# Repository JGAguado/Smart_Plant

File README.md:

# Smart Plant

**See how your plant is doing — on its own e-paper label and in Home Assistant.**

Smart Plant measures soil moisture, light, temperature and humidity. Place it
in your plant pot, read the measurements on the 2.9-inch e-paper display,
and connect it to Home Assistant with ESPHome.

**[Get started](https://smart-plant.readthedocs.io/en/v2r1/getting_started.html)**
· **[Create your plant label](https://github.com/JGAguado/Label-maker)**
· **[Get a board](https://www.elecrow.com/smart-plant.html)**
· **[Read the documentation](https://smart-plant.readthedocs.io/en/v2r1/)**

## A useful label for every plant

- **Check the soil and surroundings.** Read soil moisture, ambient light,
  air temperature and relative humidity.
- **Read it at the pot.** The e-paper screen shows the last displayed readings
  while the device sleeps.
- **Make it yours.** Give each plant its own name, illustration and gauge
  background with the companion Label-maker project.
- **Connect to Home Assistant.** Choose the native ESPHome API or retained
  MQTT readings for devices that spend most of their time asleep.
- **Run on battery.** The firmware sleeps between measurement cycles.
  The hardware also supports an optional solar cell.

## Start with one plant

1. [Get a board](https://www.elecrow.com/smart-plant.html), or use the
   [hardware design files](Design/) to explore the board.
2. Follow the [getting-started guide](https://smart-plant.readthedocs.io/en/v2r1/getting_started.html)
   and [ESPHome programming guide](https://smart-plant.readthedocs.io/en/v2r1/programming.html).
3. Set your Wi-Fi credentials and calibrate the soil sensor for your setup.
4. Add your own label background, then install the firmware.

The [standalone configuration](docs/source/files/configuration.yaml) is the
starting point for a single device. Read the
[safety instructions](https://smart-plant.readthedocs.io/en/v2r1/safety.html)
before assembly and flashing.

## Create your plant label

The companion **[Label-maker](https://github.com/JGAguado/Label-maker)**
generates printable plant labels and e-paper backgrounds from JSON or YAML
templates. Use it to add a plant name and illustration to your display.

Follow the [step-by-step label guide](docs/source/labels.rst).
Start with the [plant examples and generator](https://github.com/JGAguado/Label-maker/tree/main/1_Plants),
then follow the programming guide to use the resulting background image.
The firmware draws the live readings over that image.

## Connect one plant or several

| Setup | Starting point | During deep sleep |
| --- | --- | --- |
| One device with the native ESPHome API | [Standalone configuration](docs/source/files/configuration.yaml) | No network response; entity availability depends on Home Assistant setup. |
| Several devices with retained MQTT readings | [MQTT example](examples/multi-device/my-lemon-tree.yaml) | Last published readings remain available. |
| Shared packages with the native ESPHome API | [API example](examples/multi-device/my-lemon-tree-api.yaml) | No network response; entity availability depends on Home Assistant setup. |

The [multi-device guide](examples/multi-device/README.md) explains the shared
hardware core and transport profiles. Each device sets its identity and
credentials. Calibration and label images use shared defaults unless overridden.

## Explore the hardware

Smart Plant combines an ESP32-S2, a soil-moisture probe, environmental sensors
and an e-paper display. The repository includes board design files and
printable enclosure models.

- [Board design](Design/)
- [Enclosure models](Enclosure/)
- [Schematics and supporting files](Documentation/)
- [Technical specifications](https://smart-plant.readthedocs.io/en/v2r1/specs.html)
- [Assembly guide](https://smart-plant.readthedocs.io/en/v2r1/assembly.html)

## Questions and contributions

Use [Discussions](https://github.com/JGAguado/Smart_Plant/discussions) for
questions and ideas. Report reproducible problems in
[Issues](https://github.com/JGAguado/Smart_Plant/issues).

Contributions to firmware, documentation and examples are welcome. Describe
the problem, the change and how you verified it in your pull request.

Created by [J. G. Aguado](https://github.com/JGAguado), with contributions
from the community.

## License

This project uses [CC BY-NC-SA 4.0](LICENSE). See the license for attribution,
non-commercial use and sharing requirements.

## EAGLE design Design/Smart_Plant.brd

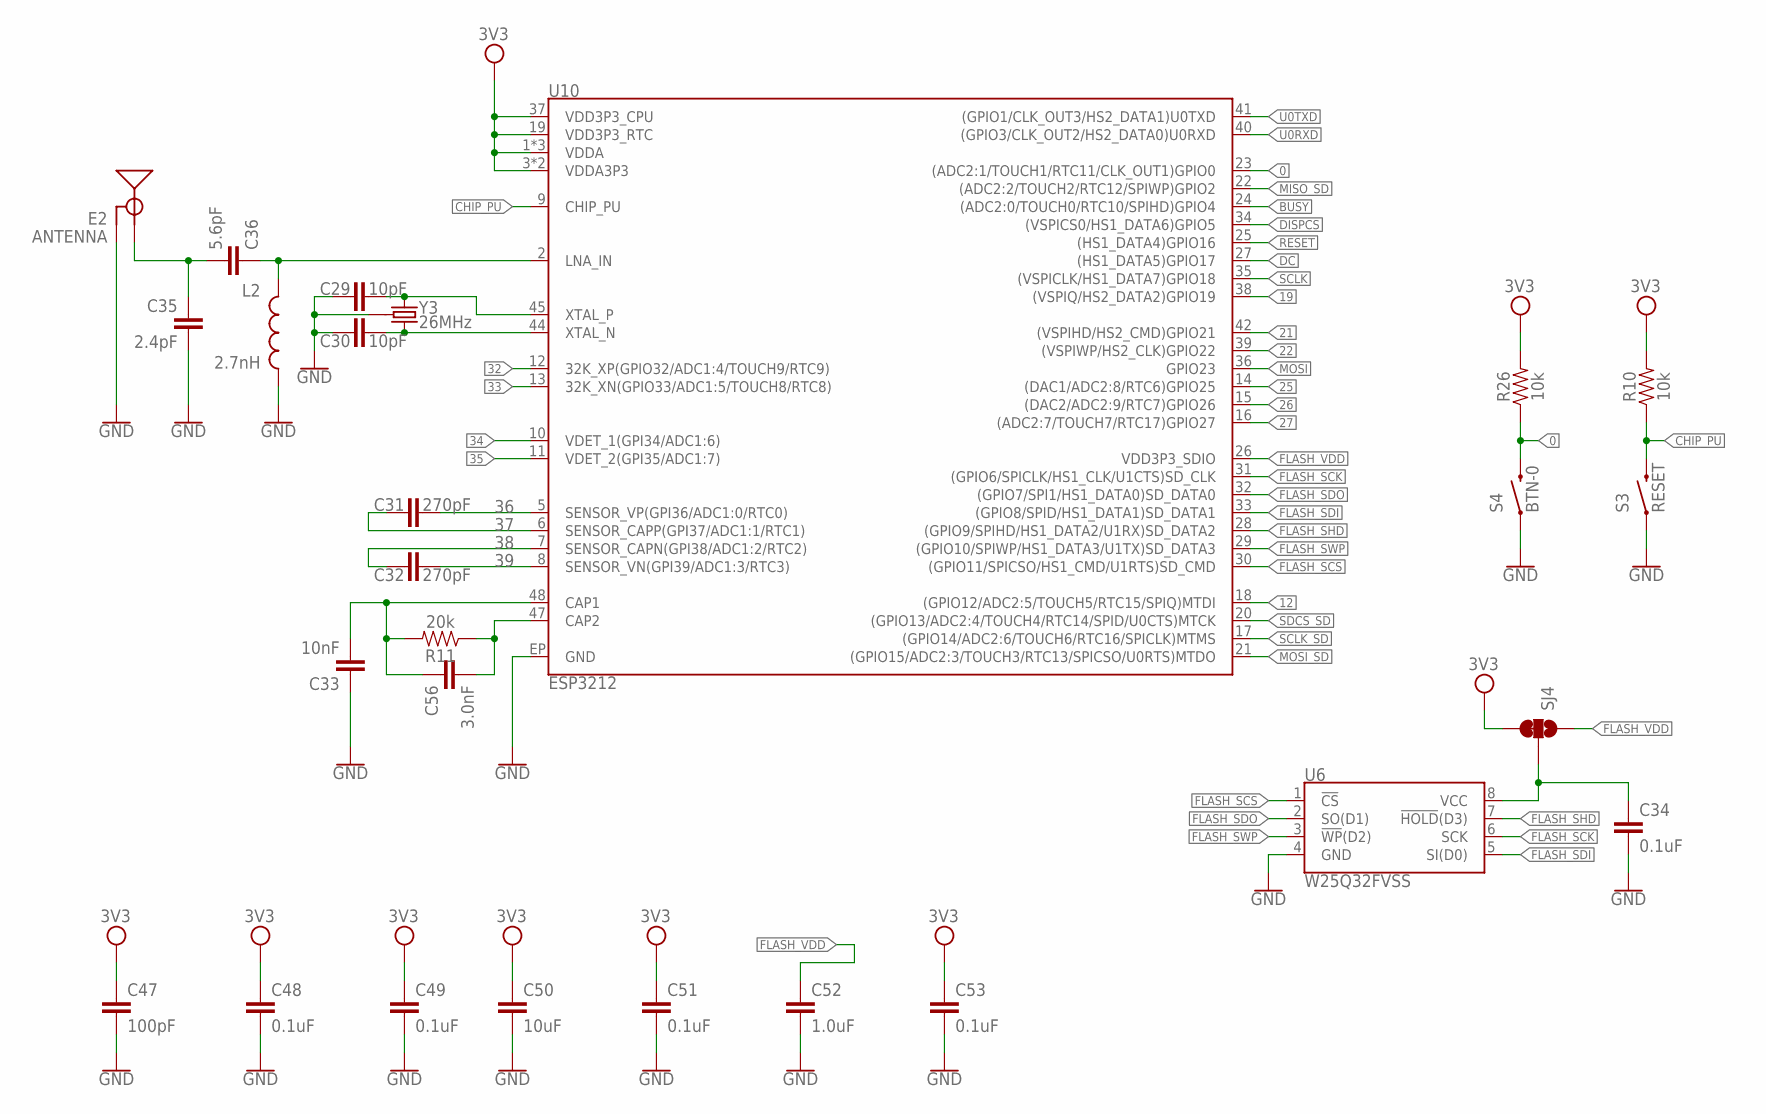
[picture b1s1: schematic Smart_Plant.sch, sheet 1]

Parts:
C29, C30: 10pF; 0603
C31, C32: 270pF; 0603
C33: 10nF; 0603
C34, C48, C49, C51, C53: 0.1uF; 0603
C35: 2.4pF; 0603
C36: 5.6pF; 0603
C47: 100pF; 0603
C50: 10uF; 0603
C52: 1.0uF; 0603
C56: 3.0nF; 0603
E2: ANTENNA; TRACE_ANTENNA_2.4GHZ_25.7MM_TUNED
L2: 2.7nH; 0603
R10, R26: 10k; 0603
R11: 20k; 0603
S3: RESET; TACTILE_SWITCH_SMD_4.6X2.8MM
S4: BTN-0; TACTILE_SWITCH_SMD_4.6X2.8MM
SJ4: JUMPER-PAD-3-2OF3_NC_BY_TRACE_SMALL; PAD-JUMPER-3-2OF3_NC_BY_TRACE_YES_SILK_FULL_BOX
U6: W25Q32FVSS; SOIC-8
U10: ESP3212; QFN48-0.4MM
Y3: 26MHz; CRYSTAL-SMD-3.2X2.5

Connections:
0: R26.1, S4.3 (2), S4.4 (2), U10.23 ((ADC2:1/TOUCH1/RTC11/CLK_OUT1)GPIO0); also elsewhere on the board
3V3: C47.1, C48.1, C49.1, C50.1, C51.1, C53.1, R10.2, R26.2, SJ4.3, U10.1 (VDDA), U10.3 (VDDA3P3), U10.4 (VDDA3P3), U10.19 (VDD3P3_RTC), U10.37 (VDD3P3_CPU), U10.43 (VDDA), U10.46 (VDDA); also elsewhere on the board
12: U10.18 ((GPIO12/ADC2:5/TOUCH5/RTC15/SPIQ)MTDI)
19: U10.38 ((VSPIQ/HS2_DATA2)GPIO19)
21: U10.42 ((VSPIHD/HS2_CMD)GPIO21)
22: U10.39 ((VSPIWP/HS2_CLK)GPIO22)
25: U10.14 ((DAC1/ADC2:8/RTC6)GPIO25)
26: U10.15 ((DAC2/ADC2:9/RTC7)GPIO26)
27: U10.16 ((ADC2:7/TOUCH7/RTC17)GPIO27)
32: U10.12 (32K_XP(GPIO32/ADC1:4/TOUCH9/RTC9))
33: U10.13 (32K_XN(GPIO33/ADC1:5/TOUCH8/RTC8))
34: U10.10 (VDET_1(GPI34/ADC1:6))
35: U10.11 (VDET_2(GPI35/ADC1:7))
36: C31.2, U10.5 (SENSOR_VP(GPI36/ADC1:0/RTC0))
37: C31.1, U10.6 (SENSOR_CAPP(GPI37/ADC1:1/RTC1))
38: C32.1, U10.7 (SENSOR_CAPN(GPI38/ADC1:2/RTC2))
39: C32.2, U10.8 (SENSOR_VN(GPI39/ADC1:3/RTC3))
BUSY: U10.24 ((ADC2:0/TOUCH0/RTC10/SPIHD)GPIO4); also elsewhere on the board
CAP_10N1: C33.2, C56.1, R11.2, U10.48 (CAP1)
CHIP_PU: R10.1, S3.3 (2), S3.4 (2), U10.9 (CHIP_PU); also elsewhere on the board
DC: U10.27 ((HS1_DATA5)GPIO17); also elsewhere on the board
DISPCS: U10.34 ((VSPICS0/HS1_DATA6)GPIO5); also elsewhere on the board
FLASH_SCK: U6.6 (SCK), U10.31 ((GPIO6/SPICLK/HS1_CLK/U1CTS)SD_CLK)
FLASH_SCS: U6.1 (!CS!), U10.30 ((GPIO11/SPICSO/HS1_CMD/U1RTS)SD_CMD)
FLASH_SDI: U6.5 (SI(D0)), U10.33 ((GPIO8/SPID/HS1_DATA1)SD_DATA1)
FLASH_SDO: U6.2 (SO(D1)), U10.32 ((GPIO7/SPI1/HS1_DATA0)SD_DATA0)
FLASH_SHD: U6.7 (!HOLD!(D3)), U10.28 ((GPIO9/SPIHD/HS1_DATA2/U1RX)SD_DATA2)
FLASH_SWP: U6.3 (!WP!(D2)), U10.29 ((GPIO10/SPIWP/HS1_DATA3/U1TX)SD_DATA3)
FLASH_VDD: C52.1, SJ4.1, U10.26 (VDD3P3_SDIO)
GND: C29.1, C30.1, C33.1, C34.2, C35.2, C47.2, C48.2, C49.2, C50.2, C51.2, C52.2, C53.2, E2.GND, E2.GND2 (GND), L2.2, S3.1, S3.2 (1), S4.1, S4.2 (1), U6.4 (GND), U10.EP (GND), Y3.2 (GND), Y3.4 (GND); also elsewhere on the board
LNA_IN1: C36.1, L2.1, U10.2 (LNA_IN)
MISO_SD: U10.22 ((ADC2:2/TOUCH2/RTC12/SPIWP)GPIO2); also elsewhere on the board
MOSI: U10.36 (GPIO23); also elsewhere on the board
MOSI_SD: U10.21 ((GPIO15/ADC2:3/TOUCH3/RTC13/SPICSO/U0RT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); also elsewhere on the board
unnamed: C34.1, SJ4.2, U6.8 (VCC)
unnamed: C29.2, U10.45 (XTAL_P), Y3.1
unnamed: C30.2, U10.44 (XTAL_N), Y3.3 (2)
unnamed: C56.2, R11.1, U10.47 (CAP2)
RESET: U10.25 ((HS1_DATA4)GPIO16); also elsewhere on the board
SCLK: U10.35 ((VSPICLK/HS1_DATA7)GPIO18); also elsewhere on the board
SCLK_SD: U10.17 ((GPIO14/ADC2:6/TOUCH6/RTC16/SPICLK)MTMS); also elsewhere on the board
SDCS_SD: U10.20 ((GPIO13/ADC2:4/TOUCH4/RTC14/SPID/U0CTS)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); also elsewhere on the board
TRACE_ANT1: C35.1, C36.2, E2.ANT (SIGNAL)
U0RXD: U10.40 ((GPIO3/CLK_OUT2/HS2_DATA0)U0RXD); also elsewhere on the board
U0TXD: U10.41 ((GPIO1/CLK_OUT3/HS2_DATA1)U0TXD); also elsewhere on the board

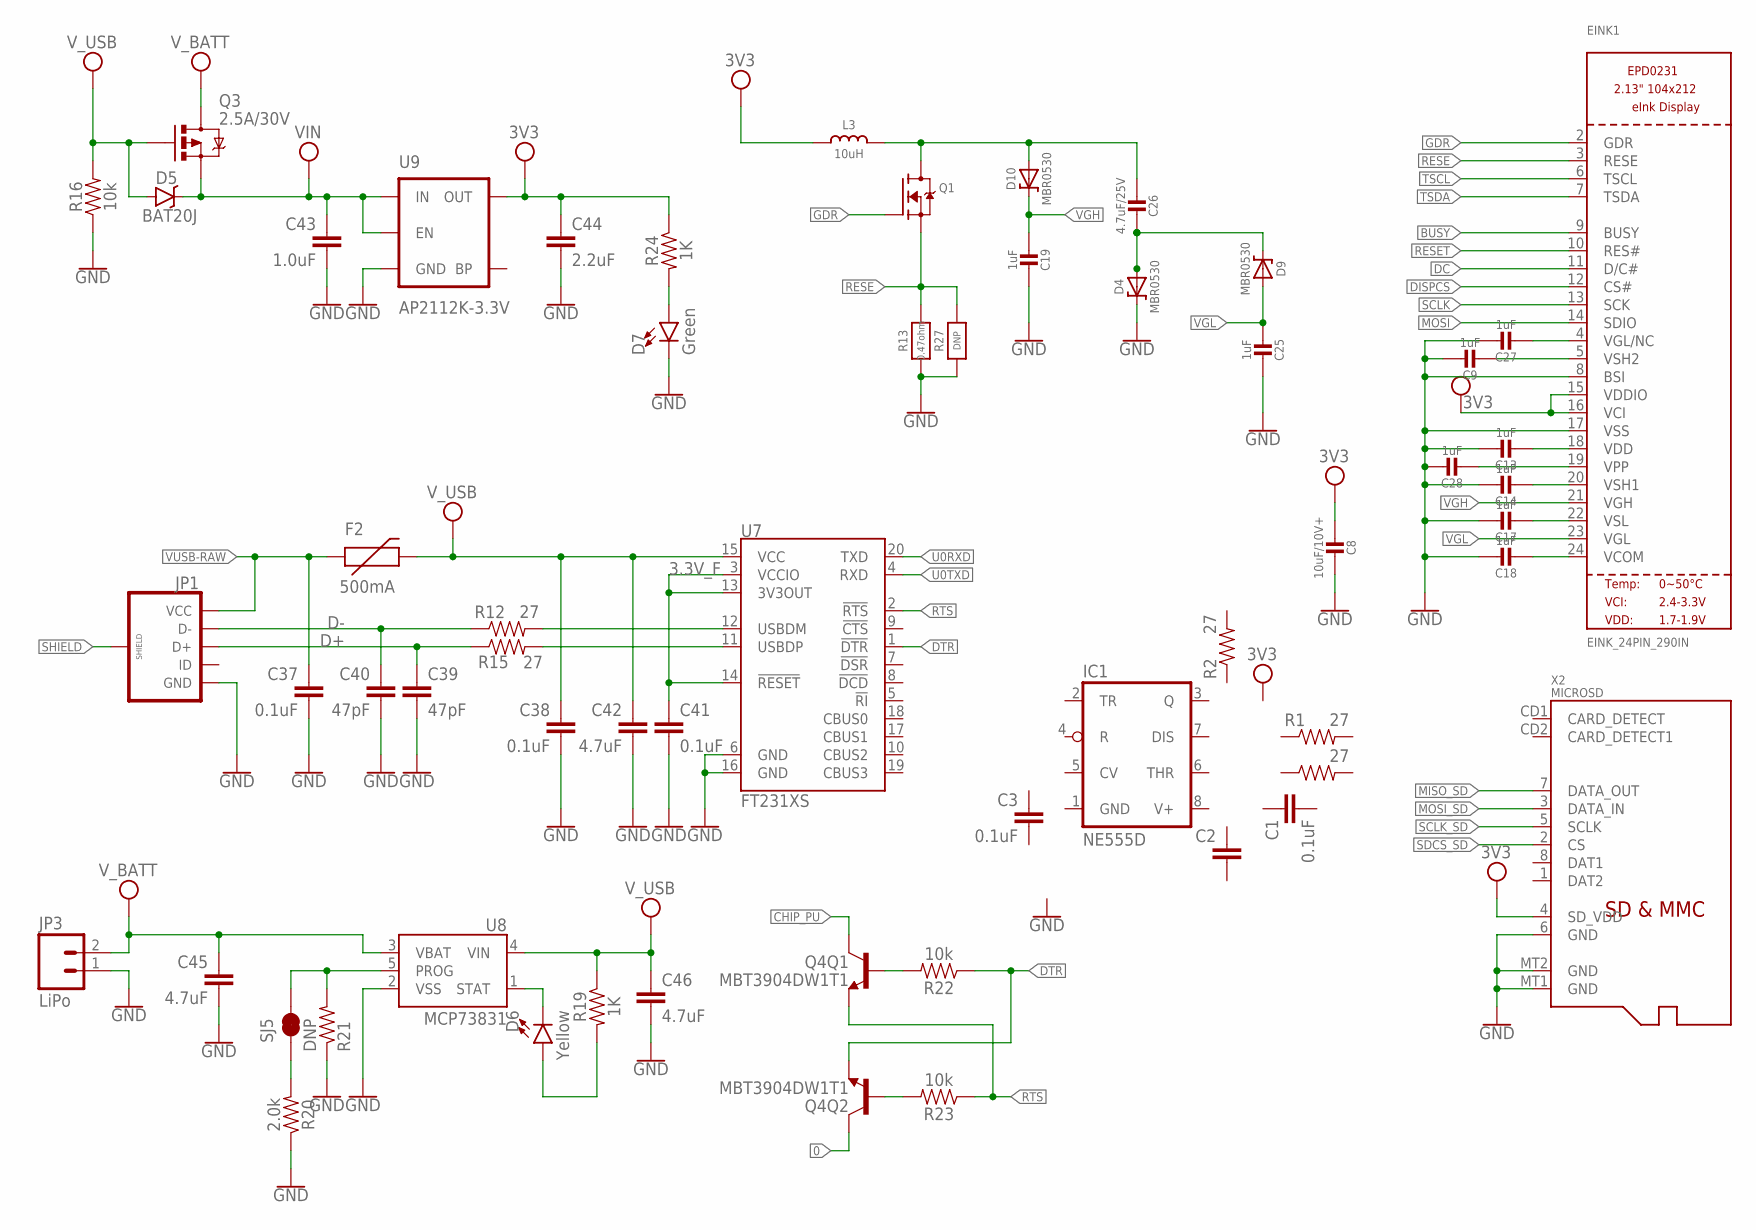
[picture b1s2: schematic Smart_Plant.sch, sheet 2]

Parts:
C1, C2, C3, C37, C38, C41: 0.1uF; 0603
C8: 10uF/10V+; 0805-NO
C9, C13, C14, C17, C18, C19, C25, C27, C28: 1uF; 0805-NO
C26: 4.7uF/25V; 0805-NO
C39, C40: 47pF; 0603
C42: 4.7uF; 0603-CAP
C43: 1.0uF; 0805
C44: 2.2uF; 0603
C45, C46: 4.7uF; 0603
D4, D9, D10: MBR0530; SOD-123
D5: BAT20J; SOD-323
D6: Yellow; LED-0603
D7: Green; LED-0603
EINK1: EINK_24PIN_290IN; EINK_290IN
F2: 500mA; PTC-1206
IC1: NE555D; SO08
JP1: USB_MICROB_PLUGCONN-11752; USB-B-MICRO-SMD_V03
JP3: LiPo; JST-2-PTH
L3: 10uH; INDUCTOR_4X4MM_NR401
Q1: IRLML0100; SOT23-3
Q3: 2.5A/30V; SOT23-3
Q4: MBT3904DW1T1; SC70-6
R1, R2, R3, R12, R15: 27; 0603
R13: 0.47ohm; 0805_10MGAP
R16, R22, R23: 10k; 0603
R19, R24: 1K; 0603
R20: 2.0k; 0603
R21: DNP; 1/6W-RES
R27: DNP; 0805_10MGAP
SJ5: JUMPER-PAD-2-NC_BY_TRACE; PAD-JUMPER-2-NC_BY_TRACE_YES_SILK
U7: FT231XS; SSOP20_L
U8: MCP73831; SOT23-5
U9: AP2112K-3.3V; SOT23-5
X2: MICROSD

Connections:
0: Q4.6 (C); also elsewhere on the board
3.3V_F: C41.1, U7.3 (VCCIO), U7.13 (3V3OUT), U7.14 (!RESET)
3V3: C8.2, C44.1, EINK1.15 (VDDIO), EINK1.16 (VCI), L3.P$2 (2), R24.1, U9.5 (OUT), X2.4 (SD_VDD); also elsewhere on the board
BUSY: EINK1.9 (BUSY); also elsewhere on the board
CHIP_PU: Q4.3 (C); also elsewhere on the board
D+: C39.1, JP1.D+, R15.1
D-: C40.1, JP1.D-, R12.1
DC: EINK1.11 (D/C#); also elsewhere on the board
DISPCS: EINK1.12 (CS#); also elsewhere on the board
DTR: Q4.1 (E), R22.1, U7.1 (!DTR)
GDR: EINK1.2 (GDR), Q1.1 (G)
GND: C8.1, C9.1, C13.1, C14.1, C17.1, C18.1, C19.2, C25.2, C27.1, C28.1, C37.2, C38.2, C39.2, C40.2, C41.2, C42.2, C43.2, C44.2, C45.2, C46.2, D4.C, D7.C, EINK1.8 (BSI), EINK1.17 (VSS), IC1.1 (GND), JP1.GND, JP3.1, R13.2, R16.1, R20.1, R21.1, R27.2, U7.6 (GND), U7.16 (GND), U8.2 (VSS), U9.2 (GND), X2.6 (GND), X2.MT1 (GND), X2.MT2 (GND); also elsewhere on the board
MISO_SD: X2.7 (DATA_OUT); also elsewhere on the board
MOSI: EINK1.14 (SDIO); also elsewhere on the board
MOSI_SD: X2.3 (DATA_IN); also elsewhere on the board
unnamed: R12.2, U7.12 (USBDM)
unnamed: C9.2, EINK1.5 (VSH2)
unnamed: C13.2, EINK1.18 (VDD)
unnamed: C14.2, EINK1.20 (VSH1)
unnamed: C17.2, EINK1.22 (VSL)
unnamed: C18.2, EINK1.24 (VCOM)
unnamed: C26.2, D4.A, D9.C
unnamed: C26.1, D10.A, L3.P$1 (1), Q1.3 (D)
unnamed: R15.2, U7.11 (USBDP)
unnamed: D6.A, R19.2
unnamed: D6.C, U8.1 (STAT)
unnamed: R21.2, SJ5.2, U8.5 (PROG)
unnamed: R20.2, SJ5.1
unnamed: Q4.5 (B), R22.2
unnamed: Q4.2 (B), R23.2
unnamed: D7.A, R24.2
unnamed: C27.2, EINK1.4 (VGL/NC)
unnamed: C28.2, EINK1.19 (VPP)
RESE: EINK1.3 (RESE), Q1.2 (S), R13.1, R27.1
RESET: EINK1.10 (RES#); also elsewhere on the board
RTS: Q4.4 (E), R23.1, U7.2 (!RTS)
SCLK: EINK1.13 (SCK); also elsewhere on the board
SCLK_SD: X2.5 (SCLK); also elsewhere on the board
SDCS_SD: X2.2 (CS); also elsewhere on the board
SHIELD: JP1.SHIELD1 (SHIELD), JP1.SHIELD2 (SHIELD), JP1.SHIELD3 (SHIELD)
TSCL: EINK1.6 (TSCL)
TSDA: EINK1.7 (TSDA)
U0RXD: U7.20 (TXD); also elsewhere on the board
U0TXD: U7.4 (RXD); also elsewhere on the board
V+: IC1.8 (V+)
VGH: C19.1, D10.C, EINK1.21 (VGH)
VGL: C25.1, D9.A, EINK1.23 (VGL)
VIN: C43.1, D5.C, Q3.2 (S), U9.1 (IN), U9.3 (EN)
VUSB-RAW: C37.1, F2.1, JP1.VBUS (VCC)
V_BATT: C45.1, JP3.2, Q3.3 (D), U8.3 (VBAT)
V_USB: C38.1, C42.1, C46.1, D5.A, F2.2, Q3.1 (G), R16.2, R19.1, U7.15 (VCC), U8.4 (VIN)

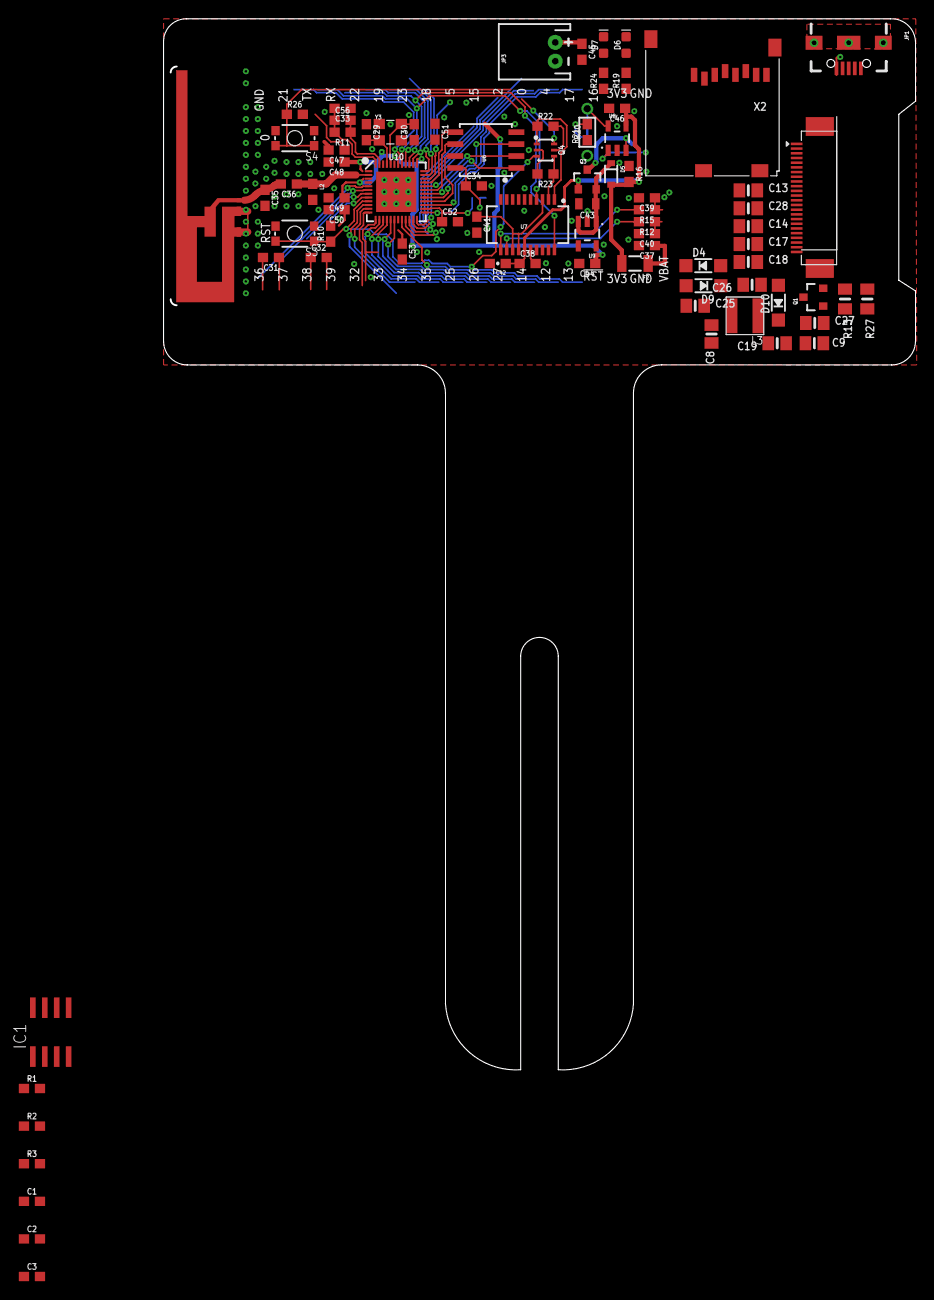
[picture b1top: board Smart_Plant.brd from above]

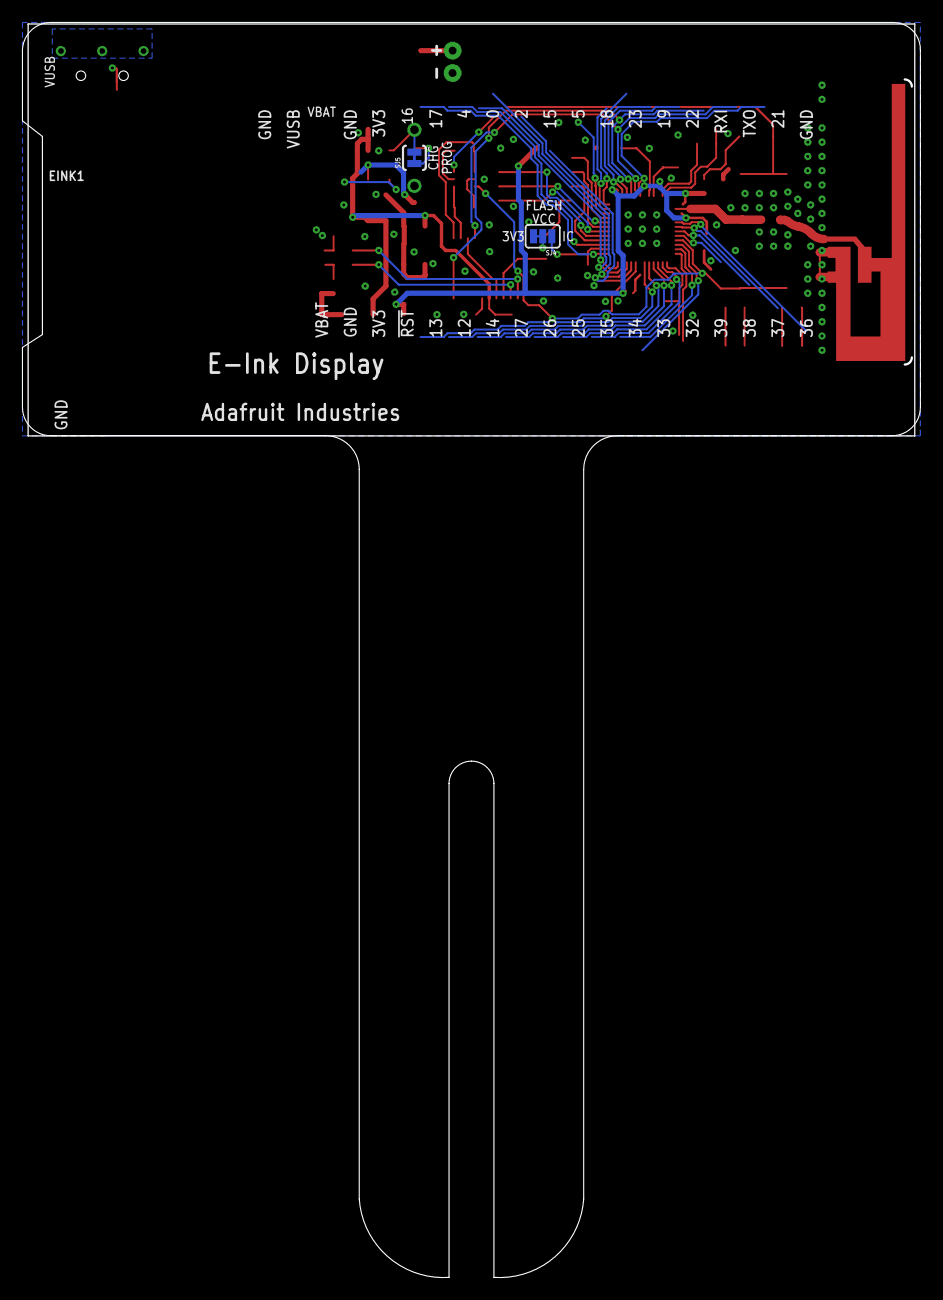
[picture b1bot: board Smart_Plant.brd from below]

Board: 2 copper layers, 80.0 x 111.8 mm, 85 parts (3 on the bottom side), 66 nets.

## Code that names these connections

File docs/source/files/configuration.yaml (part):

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
spi:
  clk_pin:  GPIO12
  mosi_pin: GPIO11
    
image:
  - platform: file
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      - "pool.ntp.org"     # fallback
switch:
  - platform: gpio
    pin: GPIO4
    id: exc
    icon: "mdi:power"
    restore_mode: ALWAYS_ON
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        
  # Capacitive soil moisture sensor
  - platform: adc
    pin: GPIO1
    name: "${friendly_name} Soil Moisture"
    id : soil
    # In order to have proper mapping in HA
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
display:
  - platform: waveshare_epaper
    cs_pin: GPIO10
    dc_pin: GPIO13
    busy_pin: GPIO${display_busy_gpio}
    reset_pin: GPIO${display_reset_gpio}
    rotation: 270
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
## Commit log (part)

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2022-04-13 Added design files
2022-04-13 Added documentation
2022-04-13 Added design files for 'Kit' branch
2022-04-13 Added design files to 'Custom' branch

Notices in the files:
README.md:
License: CC BY-NC-SA 4.0
parts and their libraries:
SparkFun-Electromechanical: Licensing: Creative Commons ShareAlike 4.0 International - https://creativecommons.org/licenses/by-sa/4.0
SparkFun-DigitalIC: Licensing: CC v3.0 Share-Alike You are welcome to use this library for commercial purposes.
